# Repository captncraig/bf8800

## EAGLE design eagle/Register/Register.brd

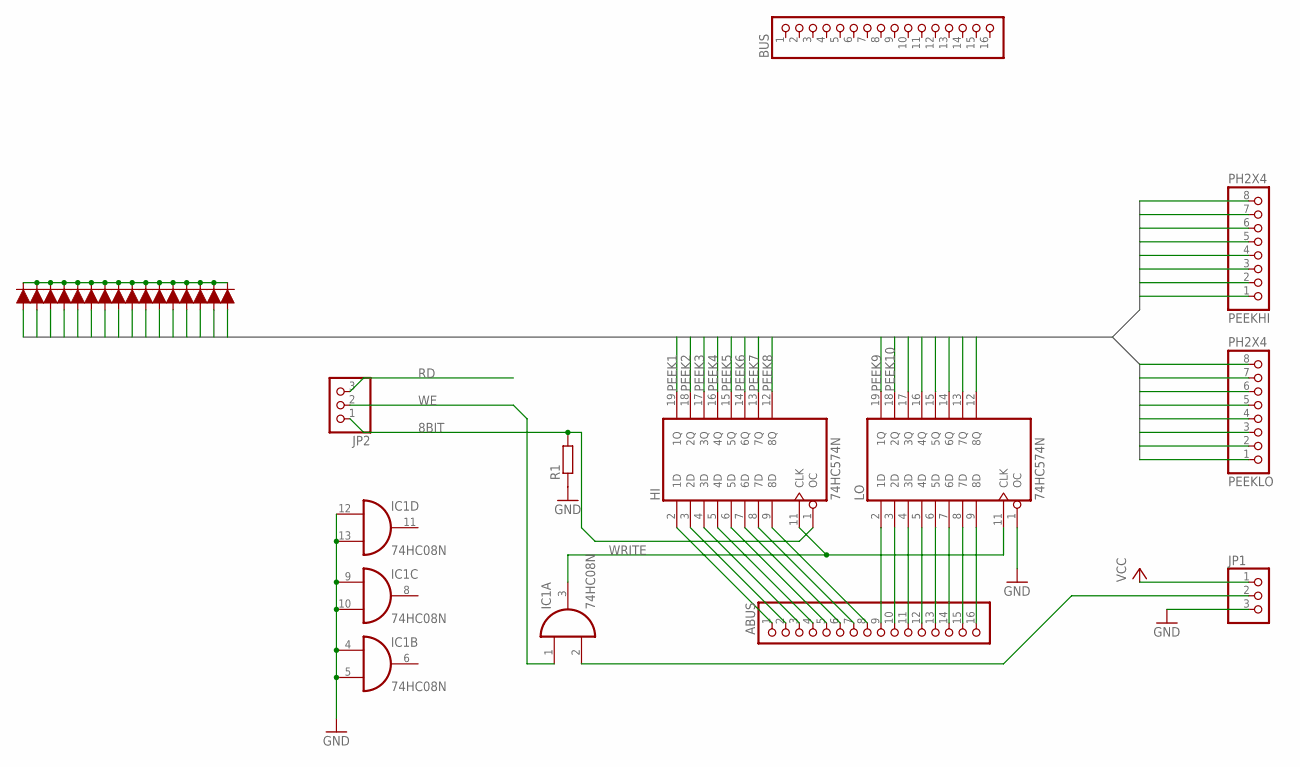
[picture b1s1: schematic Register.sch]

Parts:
ABUS: PINHD-1X16; 1X16
BUS: PINHD-1X16; 1X16
D1, D2, D3, D4, D5, D6, D7, D8, D9, D10, D11, D12, D13, D14, D15, D16: 200mA/100V/1V; DIODE-1N4148
HI: 74HC574N; DIL20
IC1: 74HC08N; DIL14
JP1, JP2: PINHD-1X3; 1X03
LO: 74HC574N; DIL20
PEEKHI: PH2X4; 2X04
PEEKLO: PH2X4; 2X04
R1: R-EU_0204/7; 0204/7

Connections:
8BIT: HI.1 (OC), JP2.1, R1.2
CLK: IC1.2 (I1), JP1.2
GND: HI.10 (GND), IC1.4 (I0), IC1.5 (I1), IC1.7 (GND), IC1.9 (I0), IC1.10 (I1), IC1.12 (I0), IC1.13 (I1), JP1.3, LO.1 (OC), LO.10 (GND), R1.1
unnamed: ABUS.9, LO.2 (1D)
unnamed: ABUS.10, LO.3 (2D)
unnamed: ABUS.11, LO.4 (3D)
unnamed: ABUS.12, LO.5 (4D)
unnamed: ABUS.13, LO.6 (5D)
unnamed: ABUS.14, LO.7 (6D)
unnamed: ABUS.15, LO.8 (7D)
unnamed: ABUS.16, LO.9 (8D)
unnamed: ABUS.8, HI.9 (8D)
unnamed: ABUS.7, HI.8 (7D)
unnamed: ABUS.6, HI.7 (6D)
unnamed: ABUS.5, HI.6 (5D)
unnamed: ABUS.4, HI.5 (4D)
unnamed: ABUS.3, HI.4 (3D)
unnamed: ABUS.2, HI.3 (2D)
unnamed: ABUS.1, HI.2 (1D)
unnamed: D1.C, D2.C, D3.C, D4.C, D5.C, D6.C, D7.C, D8.C, D9.C, D10.C, D11.C, D12.C, D13.C, D14.C, D15.C, D16.C
PEEK1: D16.A, HI.19 (1Q), PEEKHI.1
PEEK2: D15.A, HI.18 (2Q), PEEKHI.2
PEEK3: D14.A, HI.17 (3Q), PEEKHI.3
PEEK4: D1.A, HI.16 (4Q), PEEKHI.4
PEEK5: D13.A, HI.15 (5Q), PEEKHI.5
PEEK6: D2.A, HI.14 (6Q), PEEKHI.6
PEEK7: D12.A, HI.13 (7Q), PEEKHI.7
PEEK8: D3.A, HI.12 (8Q), PEEKHI.8
PEEK9: D11.A, LO.19 (1Q), PEEKLO.1
PEEK10: D4.A, LO.18 (2Q), PEEKLO.2
PEEK11: D10.A, LO.17 (3Q), PEEKLO.3
PEEK12: D5.A, LO.16 (4Q), PEEKLO.4
PEEK13: D9.A, LO.14 (6Q), LO.15 (5Q), PEEKLO.5
PEEK14: D6.A, PEEKLO.6
PEEK15: D7.A, LO.13 (7Q), PEEKLO.7
PEEK16: D8.A, LO.12 (8Q), PEEKLO.8
RD: JP2.3
VCC: HI.20 (VCC), IC1.14 (VCC), JP1.1, LO.20 (VCC)
WE: IC1.1 (I0), JP2.2
WRITE: HI.11 (CLK), IC1.3 (O), LO.11 (CLK)

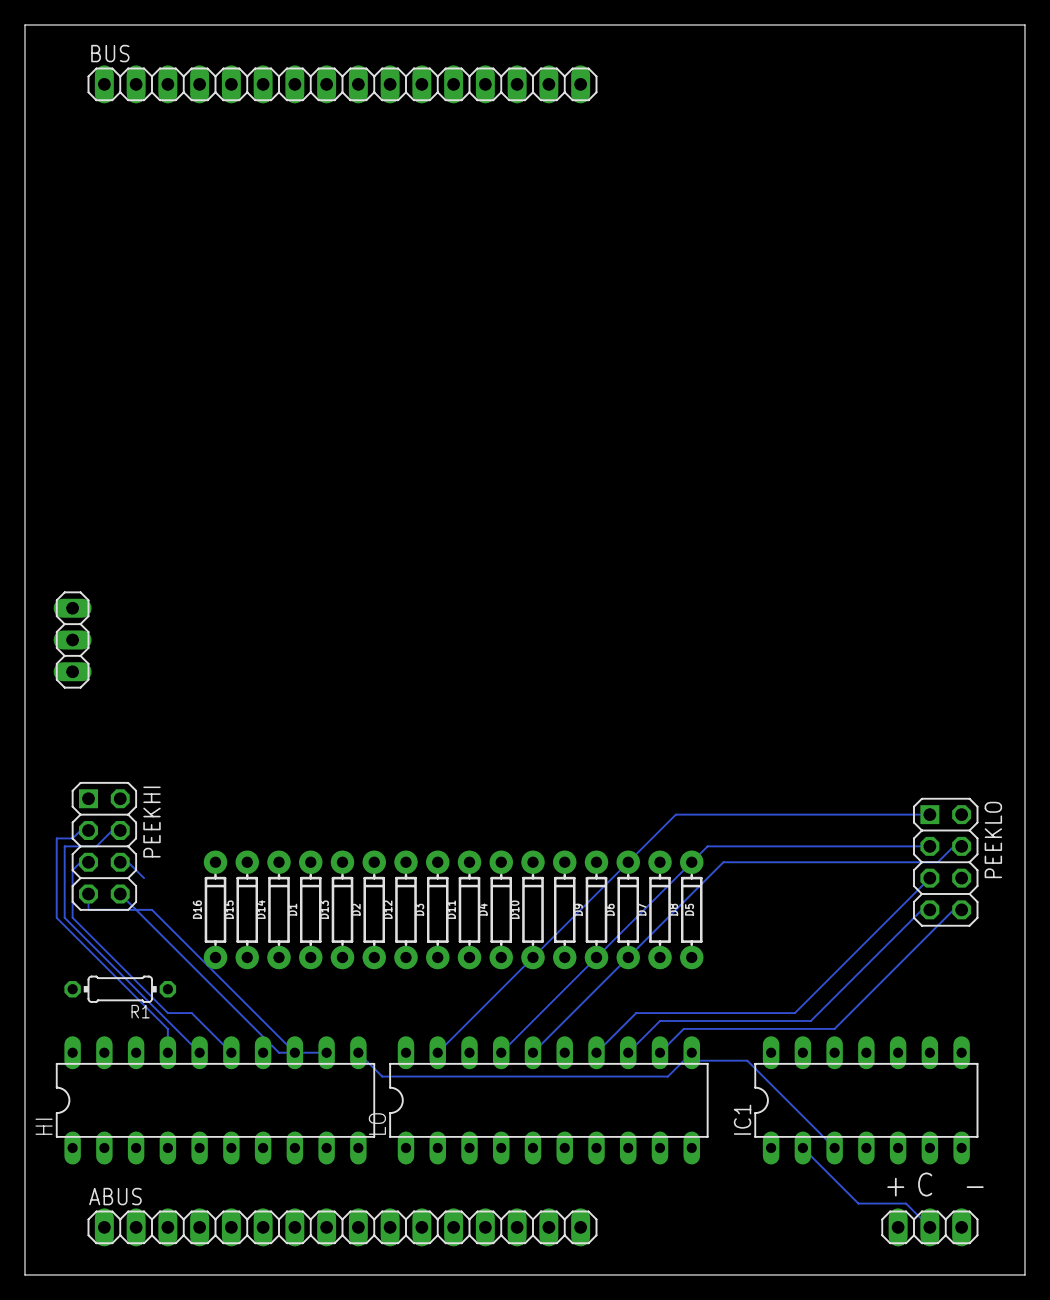
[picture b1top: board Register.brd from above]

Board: 2 copper layers, 80.0 x 100.0 mm, 26 parts (0 on the bottom side), 39 nets.

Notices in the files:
parts and their libraries:
SparkFun-DiscreteSemi: Licensing: Creative Commons ShareAlike 4.0 International - https://creativecommons.org/licenses/by-sa/4.0
